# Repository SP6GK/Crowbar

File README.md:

# **Overvoltage Protection Circuit**

This circuit is designed for **overvoltage protection** of amateur radio transceivers, which are typically powered by 13.8 V DC with a current of 20 to 25 A.

---

## **Specification**

- **Default tripping voltage**: 14.7 V  
- **Action time**: < 15 µs (typical ~µ4 s)  
- **Rated current**: Max 25 A
- **Dimension**: 94x59 mm

---

## **Description**

The protection is achieved by **shorting the power supply**, which should blow a fuse and prevent expensive equipment from experiencing a voltage spike. The tripping voltage is approximately **14.7 V**, but it can be adjusted by replacing the Zener diode.  

For **low idle current** and **fast activation** of the triac's gate, the circuit uses an additional transistor in a configuration similar to a Zener-NPN regulator.  

The PCB features space for **M5 screw terminals**, but wires can also be soldered directly and four M3 mounting screws.

> **Recommended Use:**  
> This circuit is especially useful for linear power supplies. In the event of a final transistor(s) fault, a short between the emitter and collector could result in the full rectified voltage being present at the output, which would exceed 13.8 V.  

---

## **PCB Layout**

Below is the layout of the PCB:  

---

## **Oscilloscope Screenshots**

The oscilloscope captures below demonstrate the **input (blue, CH2)** and **output (yellow, CH1)** when a sudden 20 V was applied using two parallel 5 A power supplies.  

> Generating consistent transients was challenging, but these scenarios show how the circuit prevented the voltage rail from ramping up and successfully clamped the voltage.  

1. **Transient 1**  

2. **Transient 2**  

3. **Transient 3**

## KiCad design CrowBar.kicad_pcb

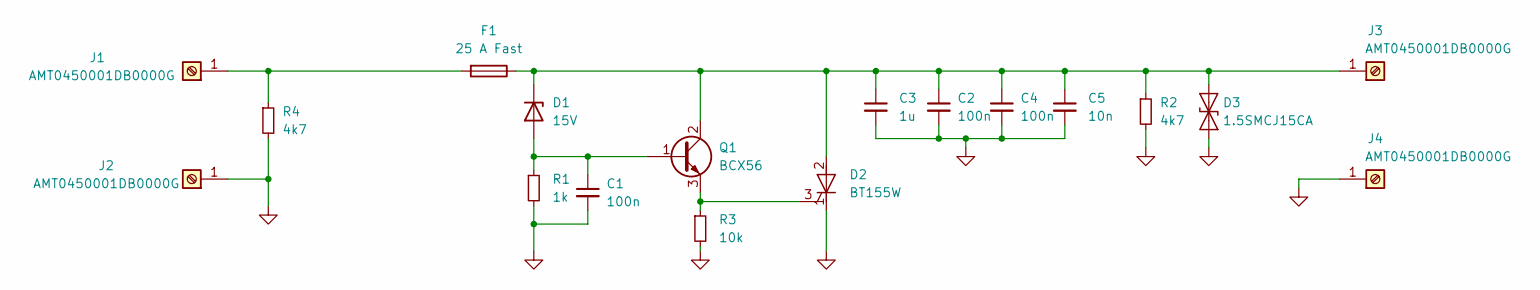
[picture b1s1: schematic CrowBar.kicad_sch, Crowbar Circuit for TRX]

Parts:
C1, C2, C4: 100n; C_0805_2012Metric
C3: 1u; C_0805_2012Metric
C5: 10n; C_0805_2012Metric
D1: 15V; D_SOD-123F
D2: BT155W; TO-247-3_Horizontal_TabDown
D3: 1.5SMCJ15CA; D_SMC
F1: 25 A Fast; 8040.0001SCHURTER
J1, J2, J3, J4: AMT0450001DB0000G
Q1: BCX56; SOT-89-3
R1: 1k; R_0805_2012Metric_Pad1.20x1.40mm_HandSolder
R2, R4: 4k7; R_1206_3216Metric_Pad1.30x1.75mm_HandSolder
R3: 10k; R_0805_2012Metric_Pad1.20x1.40mm_HandSolder

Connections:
GND: C1.2, C2.2, C3.2, C4.2, C5.2, D2.1 (K), D3.2 (A2), J2.1, J4.1, R1.2, R2.2, R3.2, R4.2
unnamed: C1.1, D1.2 (A), Q1.1 (B), R1.1
unnamed: C2.1, C3.1, C4.1, C5.1, D1.1 (K), D2.2 (A), D3.1 (A1), F1.1, J3.1, Q1.2 (C), R2.1
unnamed: D2.3 (G), Q1.3 (E), R3.1
unnamed: F1.2, J1.1, R4.1

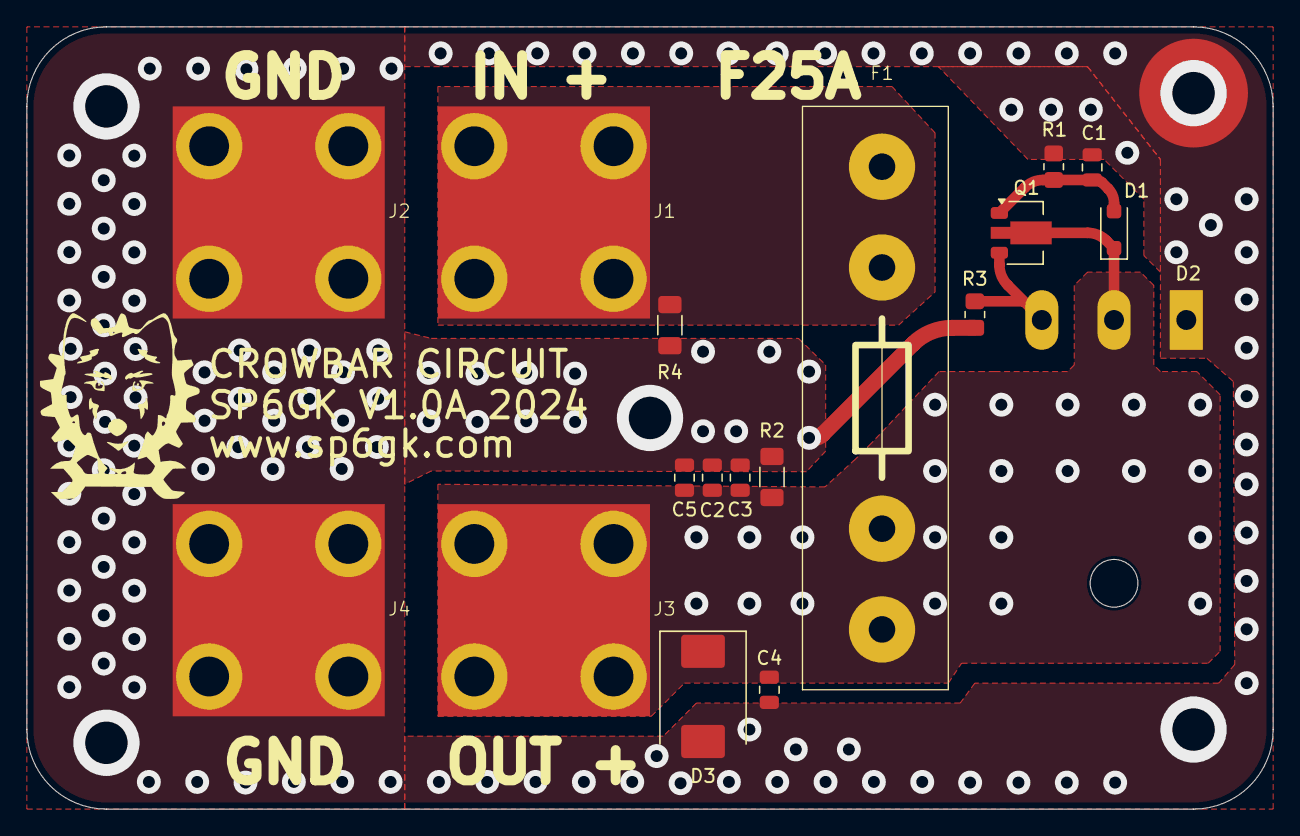
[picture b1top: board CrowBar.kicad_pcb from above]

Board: 2 copper layers, 94.0 x 59.0 mm, 18 parts (0 on the bottom side), 5 nets.
